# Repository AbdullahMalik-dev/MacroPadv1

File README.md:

# Abdullah's MacroPad
### Inspiration

I wanted to create this macropad because this project will be my first step into creatinv my first PCB and 3d model.

### Challenges

This was my first time using AutoDesk Fusion, and using Kicad, and I enjoyed every bit of it. I want to explore more and I want to build bigger and better projects that I have in mind.

### Specifications

BOM: 
- 4x Cherry MX Switches
- 2x SK6812 MINI Leds
- 1x XIAO RP2040
- 4x Blank DSA Keycaps
- 4x M3x16 Bolt
- 4x M3 Heatset

Others:
- KMK Firmware
- Both Bottom and Top case in the design folder as required.

Case Design            |  PCB         |   Schematics
:-------------------------:|:-------------------------:|:-------------------------:|
    |    |

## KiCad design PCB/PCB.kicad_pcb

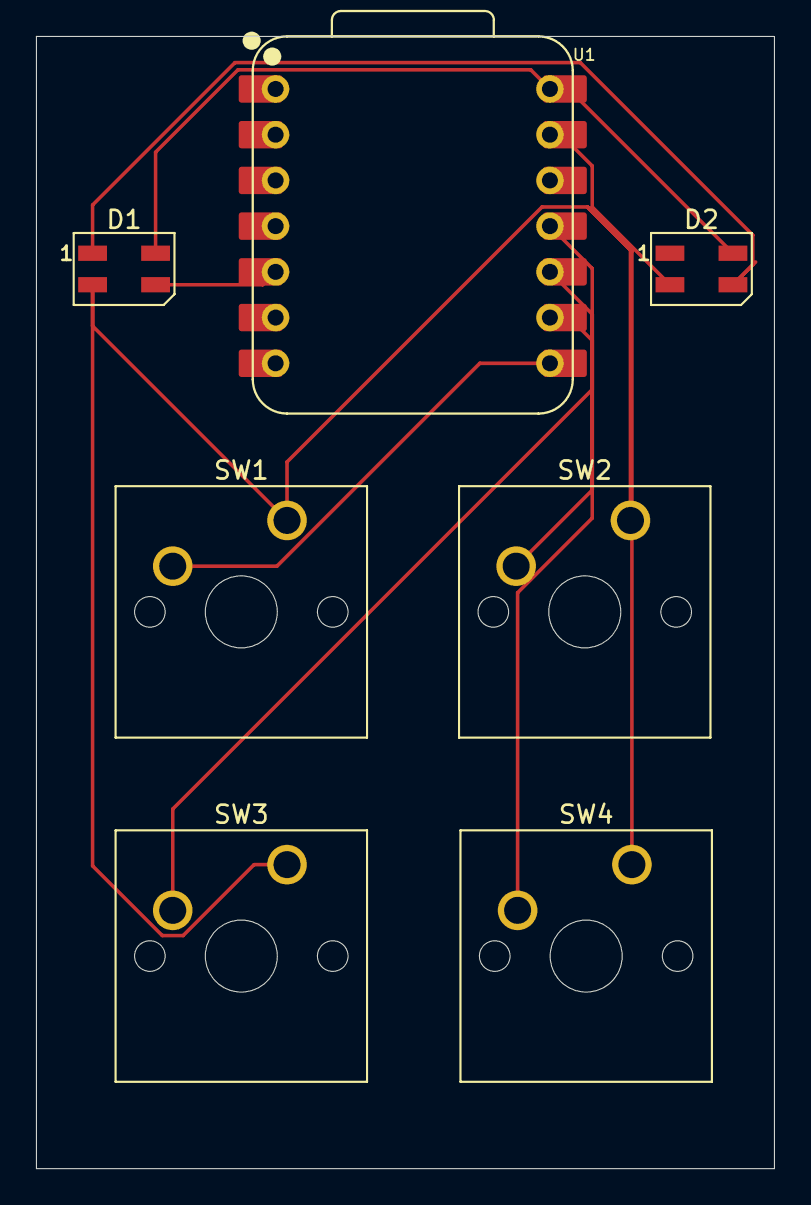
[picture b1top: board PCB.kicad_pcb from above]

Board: 2 copper layers, 41.0 x 62.9 mm, 7 parts (0 on the bottom side), 6 nets.

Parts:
D1, D2: SK6812MINI; LED_SK6812MINI_PLCC4_3.5x3.5mm_P1.75mm
SW1, SW2, SW3, SW4: SW_Push; SW_Cherry_MX_1.00u_PCB
U1: XIAO-RP2040-DIP

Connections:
+5V: D1.4 (VDD), D2.4 (VDD), U1.14 (VBUS)
GND: D1.2 (VSS), D2.2 (VSS), SW1.1, SW2.1, SW3.1, SW4.1, U1.13 (GND)
unnamed: D1.3 (DIN), U1.5 (GPIO6/SDA)
unnamed: D1.1 (DOUT), D2.3 (DIN)
unnamed: SW1.2, U1.8 (GPIO1/RX)
unnamed: SW2.2, SW3.2, SW4.2, U1.9 (GPIO2/SCK), U1.10 (GPIO4/MISO), U1.11 (GPIO3/MOSI)

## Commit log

2025-12-03 README.md
